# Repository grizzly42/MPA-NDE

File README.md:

# Antenna Deployment Mechanism

## Project Overview
This project is part of the **Nanosatellite Design and Electronics (MPA-NDE 24/25L)** course at **Brno University of Technology (BUT), Faculty of Electrical Engineering and Communication (FEEC)**. Our team is developing an **Antenna Deployment Mechanism** for a CubeSat-class nanosatellite.

## Purpose
The Antenna Deployment Mechanism (ADM) is designed to stow and deploy a flexible metal tape antenna reliably once the satellite reaches its operational orbit. The mechanism ensures the antenna remains secured during launch and deploys upon receiving an activation signal from the microcontroller unit (MCU).

## Key Features
- **Compact and Lightweight Design** – Optimized for CubeSat integration.
- **Reliable Deployment** – Ensures consistent antenna extension in space conditions.
- **Locking Mechanism** – Holds the antenna in place until deployment is required.
- **MCU Controlled Activation** – Deployment triggered via command.

## Components
- **Flexible Metal Tape Antenna**
- **Holding Mechanism (Damping System, Hinges, and Latch)**
- **Microcontroller (MCU) and Activation Circuitry**
- **Sensors for Deployment Verification**

## Block diagram

## SW (Dodělat podle skutečnosti)

```c
   DE2-PROJECT          
   ├── include         // Included file(s)
   │   └── timer.h
   ├── lib             // Libraries
   │   ├── gpio        // Your GPIO library
   │   │   ├── gpio.c
   │   │   └── gpio.h
   │   ├── oled        
   │   │   ├── oled.c
   │   │   ├── oled.h
   │   │   └── font.h
   │   ├── uart       
   │   │   ├── uart.c
   │   │   └── uart.h
   │   ├── twi       
   │   │   ├── twi.c
   │   │   └── twi.h
   │   ├── soil       
   │   │   ├── soil.c
   │   │   └── soil.h
   │   ├── controls       
   │   │   ├── controls.c
   │   │   └── controls.
   │   ├── HumTempSensor       
   │   │   ├── HumTempSensor.c
   │   │   └── HumTempSensor.h
   │   ├── rtc       
   │   │   ├── rtc.c
   │   │   └── rtc.h
   │   ├── display       
   │   │   ├── display.c
   │   │   └── display.h
   │   ├── buttons       
   │   │   ├── buttons.c
   │   │   └── buttons.h
   │   ├── pot       
   │   │   ├── pot.c
   │   │   └── pot.h
   │   └── light       
   │       ├── light.c
   │       └── light.h
   ├── src             // Source file(s)
   │   └── main.c
   ├── test            // No need this
   └── platformio.ini  // Project Configuration File
   ```

## Team
This project is developed by students of **MPA-NDE 24/25L** at BUT FEEC as part of a nanosatellite technology research initiative.

## Future Work
- Prototype development and testing.
- Thermal and mechanical stress analysis.
- Integration with satellite subsystems.

## License
This project is for academic and research purposes under the Nanosatellite Design and Electronics course at BUT.

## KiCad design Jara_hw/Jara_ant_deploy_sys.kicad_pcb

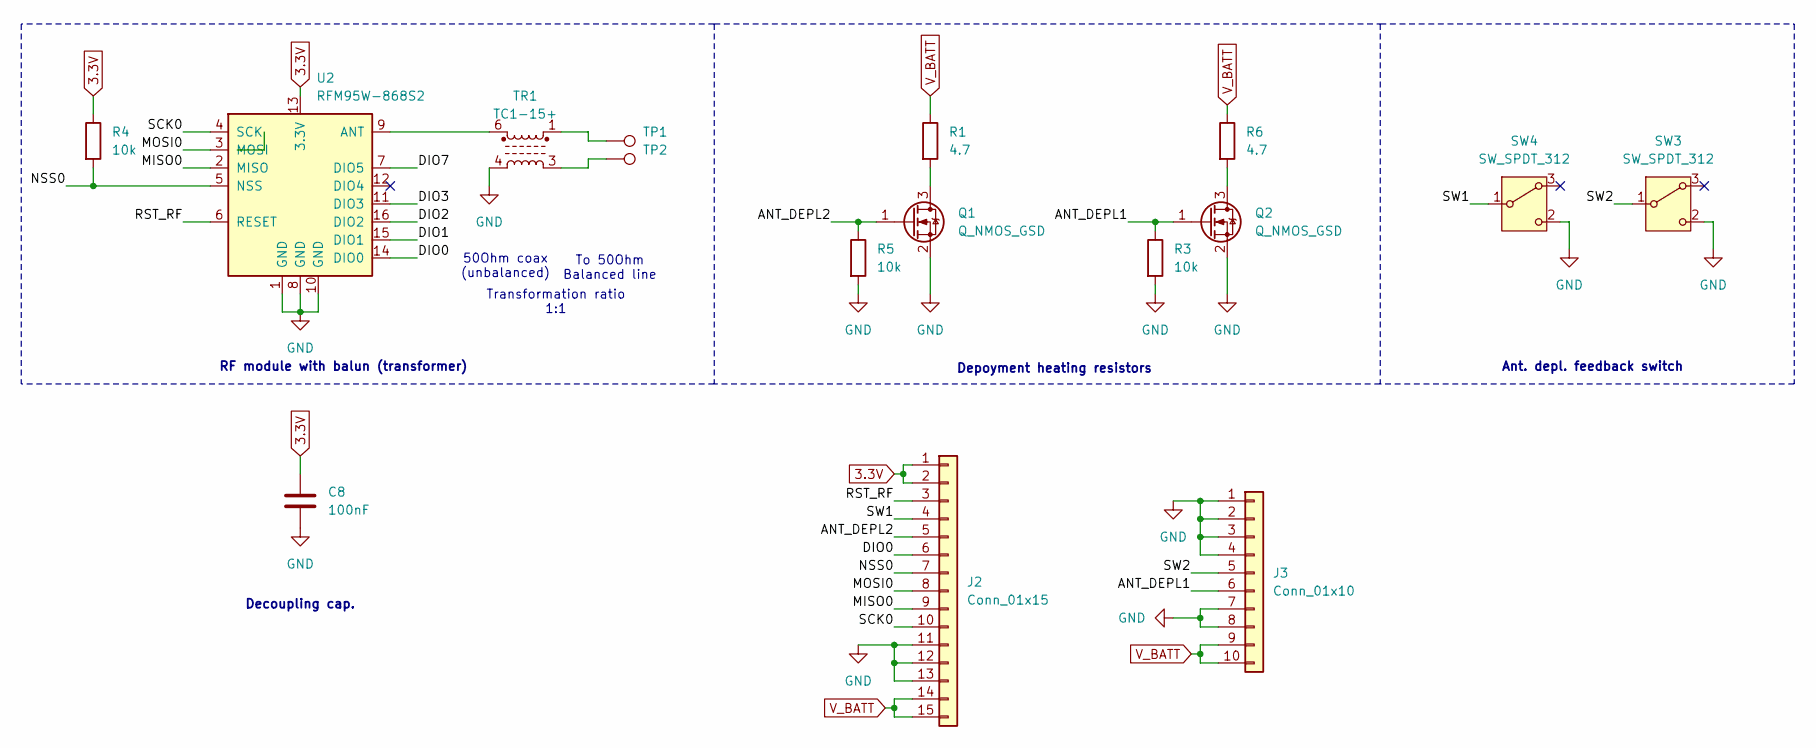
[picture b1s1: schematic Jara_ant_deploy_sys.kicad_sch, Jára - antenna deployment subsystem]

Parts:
C8: 100nF; C_0805_2012Metric
J2: Conn_01x15; PinHeader_1x15_P2.54mm_Vertical
J3: Conn_01x10; PinHeader_1x10_P2.54mm_Vertical
Q1, Q2: Q_NMOS_GSD; SOT-23
R1, R6: 4.7; R_0805_2012Metric
R3, R4, R5: 10k; R_0805_2012Metric
SW3, SW4: SW_SPDT_312; ZMA00A080L04RC
TP1, TP2: TestPoint_Pad_1.5x1.5mm
TR1: TC1-15+; Transformer_MiniCircuits_AT224-1A
U2: RFM95W-868S2; HOPERF_RFM9XW_SMD

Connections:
3.3V: C8.1, J2.1, J2.2, R4.1, U2.13 (3.3V)
/ANT_DEPL1: J3.6, Q2.1 (G), R3.1
/ANT_DEPL2: J2.5, Q1.1 (G), R5.1
/DIO0: J2.6, U2.14 (DIO0)
/DIO1: U2.15 (DIO1)
/DIO2: U2.16 (DIO2)
/DIO3: U2.11 (DIO3)
/DIO7: U2.7 (DIO5)
/MISO0: J2.9, U2.2 (MISO)
/MOSI0: J2.8, U2.3 (MOSI)
/NSS0: J2.7, R4.2, U2.5 (NSS)
/RST_RF: J2.3, U2.6 (RESET)
/SCK0: J2.10, U2.4 (SCK)
/SW1: J2.4, SW4.1 (B)
/SW2: J3.5, SW3.1 (B)
GND: C8.2, J2.11, J2.12, J2.13, J3.1, J3.2, J3.3, J3.4, J3.7, J3.8, Q1.2 (S), Q2.2 (S), R3.2, R5.2, SW3.2 (C), SW4.2 (C), TR1.4, U2.1 (GND), U2.8 (GND), U2.10 (GND)
unnamed: Q1.3 (D), R1.2
unnamed: Q2.3 (D), R6.2
unnamed: TP1.1, TR1.1
unnamed: TP2.1, TR1.3
unnamed: TR1.6, U2.9 (ANT)
V_BATT: J2.14, J2.15, J3.9, J3.10, R1.1, R6.1

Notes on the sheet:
RF module with balun (transformer)
Decoupling cap.
50Ohm coax (unbalanced)
To 50Ohm Balanced line
Ant. depl. feedback switch
Depoyment heating resistors
Transformation ratio 1:1

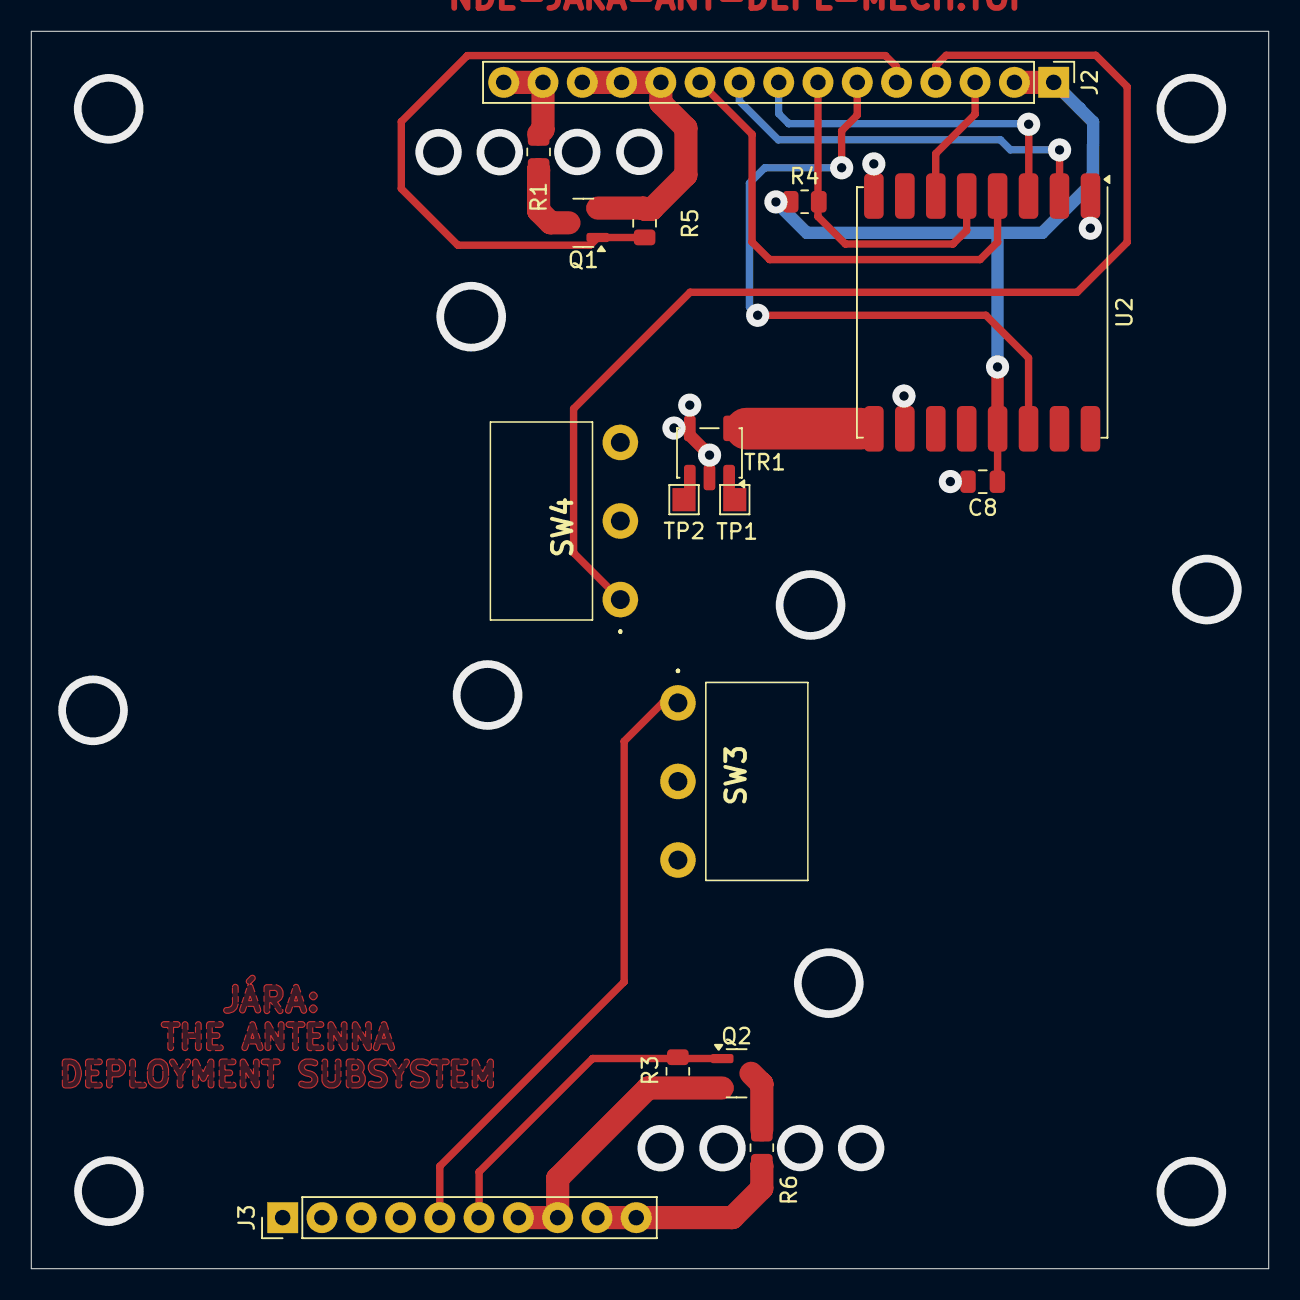
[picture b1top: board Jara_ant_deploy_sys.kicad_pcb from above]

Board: 2 copper layers, 80.0 x 80.0 mm, 16 parts (0 on the bottom side), 18 nets.

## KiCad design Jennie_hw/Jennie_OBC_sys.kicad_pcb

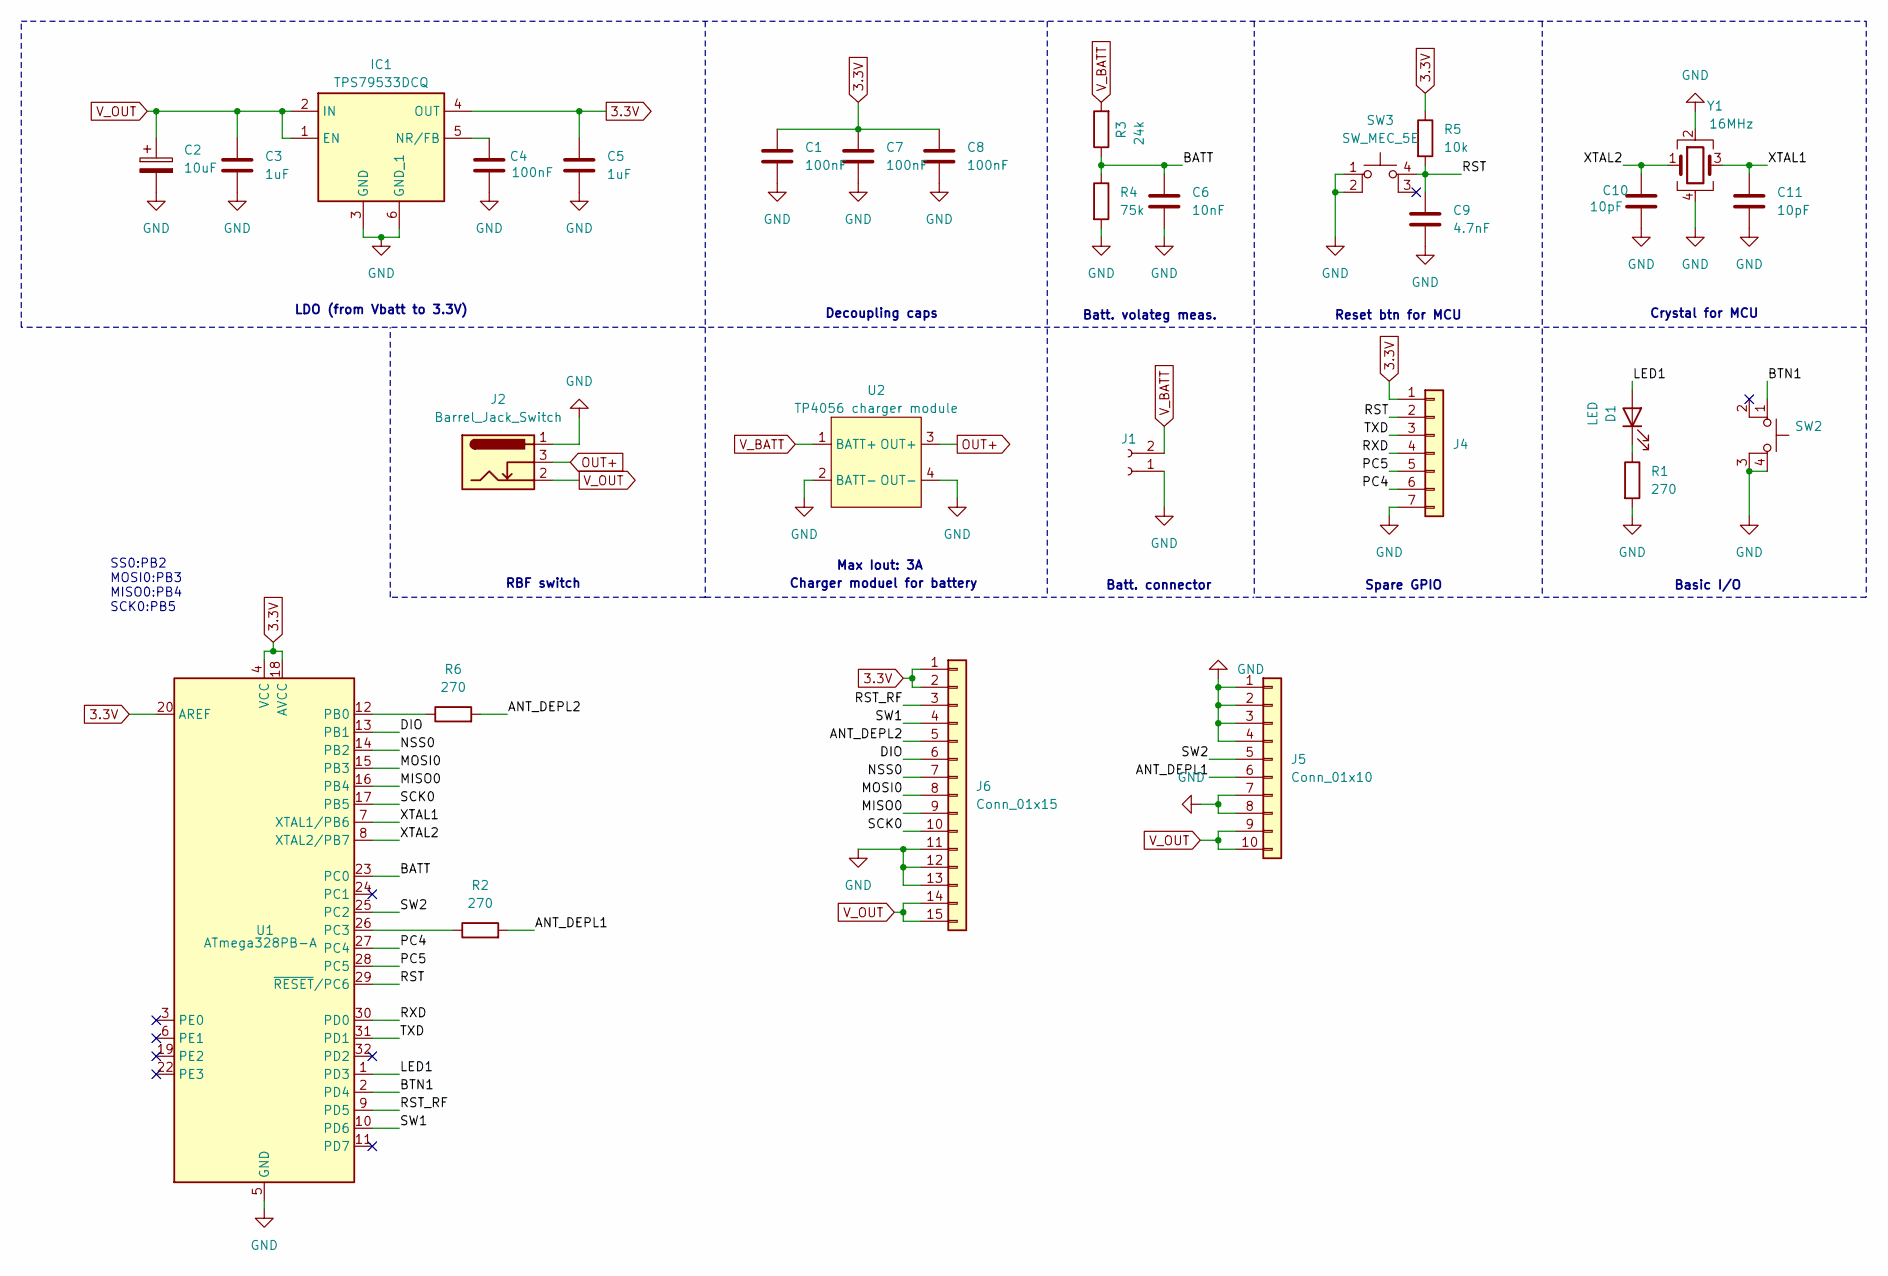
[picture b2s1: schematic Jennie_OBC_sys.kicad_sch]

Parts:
C1, C4, C7, C8: 100nF; C_0805_2012Metric
C2: 10uF; CP_Radial_D5.0mm_P2.50mm
C3, C5: 1uF; C_0805_2012Metric
C6: 10nF; C_0805_2012Metric
C9: 4.7nF; C_0805_2012Metric
C10, C11: 10pF; C_0805_2012Metric
D1: LED; LED_0805_2012Metric
IC1: TPS79533DCQ; SOT-223-6; Mouser Part Number 595-TPS79533DCQ
J1: PinHeader_1x02_P2.54mm_Vertical
J2: Barrel_Jack_Switch; BarrelJack_Horizontal
J4: PinHeader_1x07_P2.54mm_Vertical
J5: Conn_01x10; PinHeader_1x10_P2.54mm_Vertical
J6: Conn_01x15; PinHeader_1x15_P2.54mm_Vertical
R1, R2, R6: 270; R_0805_2012Metric
R3: 24k; R_0805_2012Metric
R4: 75k; R_0805_2012Metric
R5: 10k; R_0805_2012Metric
SW2: 15715272
SW3: SW_MEC_5E; 15715272
U1: ATmega328PB-A; TQFP-32_7x7mm_P0.8mm
U2: TP4056 charger module; TP4056_module
Y1: 16MHz; Crystal_SMD_3225-4Pin_3.2x2.5mm

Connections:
3.3V: C1.1, C5.1, C7.1, C8.1, IC1.4 (OUT), J4.1, J6.1, J6.2, R5.1, U1.4 (VCC), U1.18 (AVCC), U1.20 (AREF)
/ANT_DEPL1: J5.6, R2.2
/ANT_DEPL2: J6.5, R6.2
/BATT: C6.1, R3.1, R4.1, U1.23 (PC0)
/BTN1: SW2.1, U1.2 (PD4)
/DIO: J6.6, U1.13 (PB1)
/LED1: D1.2 (A), U1.1 (PD3)
/MISO0: J6.9, U1.16 (PB4)
/MOSI0: J6.8, U1.15 (PB3)
/NSS0: J6.7, U1.14 (PB2)
/PC4: J4.6, U1.27 (PC4)
/PC5: J4.5, U1.28 (PC5)
/RST: C9.1, J4.2, R5.2, SW3.4 (A), U1.29 (~RESET/PC6)
/RST_RF: J6.3, U1.9 (PD5)
/RXD: J4.4, U1.30 (PD0)
/SCK0: J6.10, U1.17 (PB5)
/SW1: J6.4, U1.10 (PD6)
/SW2: J5.5, U1.25 (PC2)
/TXD: J4.3, U1.31 (PD1)
/XTAL1: C11.1, U1.7 (XTAL1/PB6), Y1.3
/XTAL2: C10.1, U1.8 (XTAL2/PB7), Y1.1
GND: C1.2, C2.2, C3.2, C4.2, C5.2, C6.2, C7.2, C8.2, C9.2, C10.2, C11.2, IC1.3 (GND), IC1.6 (GND_1), J1.1, J2.1, J4.7, J5.1, J5.2, J5.3, J5.4, J5.7, J5.8, J6.11, J6.12, J6.13, R1.2, R4.2, SW2.3 (K), SW2.4 (A), SW3.1, SW3.2, U1.5 (GND), U1.21 (GND), U2.2 (BATT-), U2.4 (OUT-), Y1.2, Y1.4
unnamed: D1.1 (K), R1.1
unnamed: C4.1, IC1.5 (NR/FB)
unnamed: R6.1, U1.12 (PB0)
unnamed: R2.1, U1.26 (PC3)
OUT+: J2.3, U2.3 (OUT+)
V_BATT: J1.2, R3.2, U2.1 (BATT+)
V_OUT: C2.1, C3.1, IC1.1 (EN), IC1.2 (IN), J2.2, J5.9, J5.10, J6.14, J6.15

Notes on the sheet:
Batt. connector
Decoupling caps
Basic I/O
Batt. volateg meas.
Charger moduel for battery
Spare GPIO
Max Iout: 3A
RBF switch
Crystal for MCU
Reset btn for MCU
SS0:PB2 MOSI0:PB3 MISO0:PB4 SCK0:PB5
LDO (from Vbatt to 3.3V)

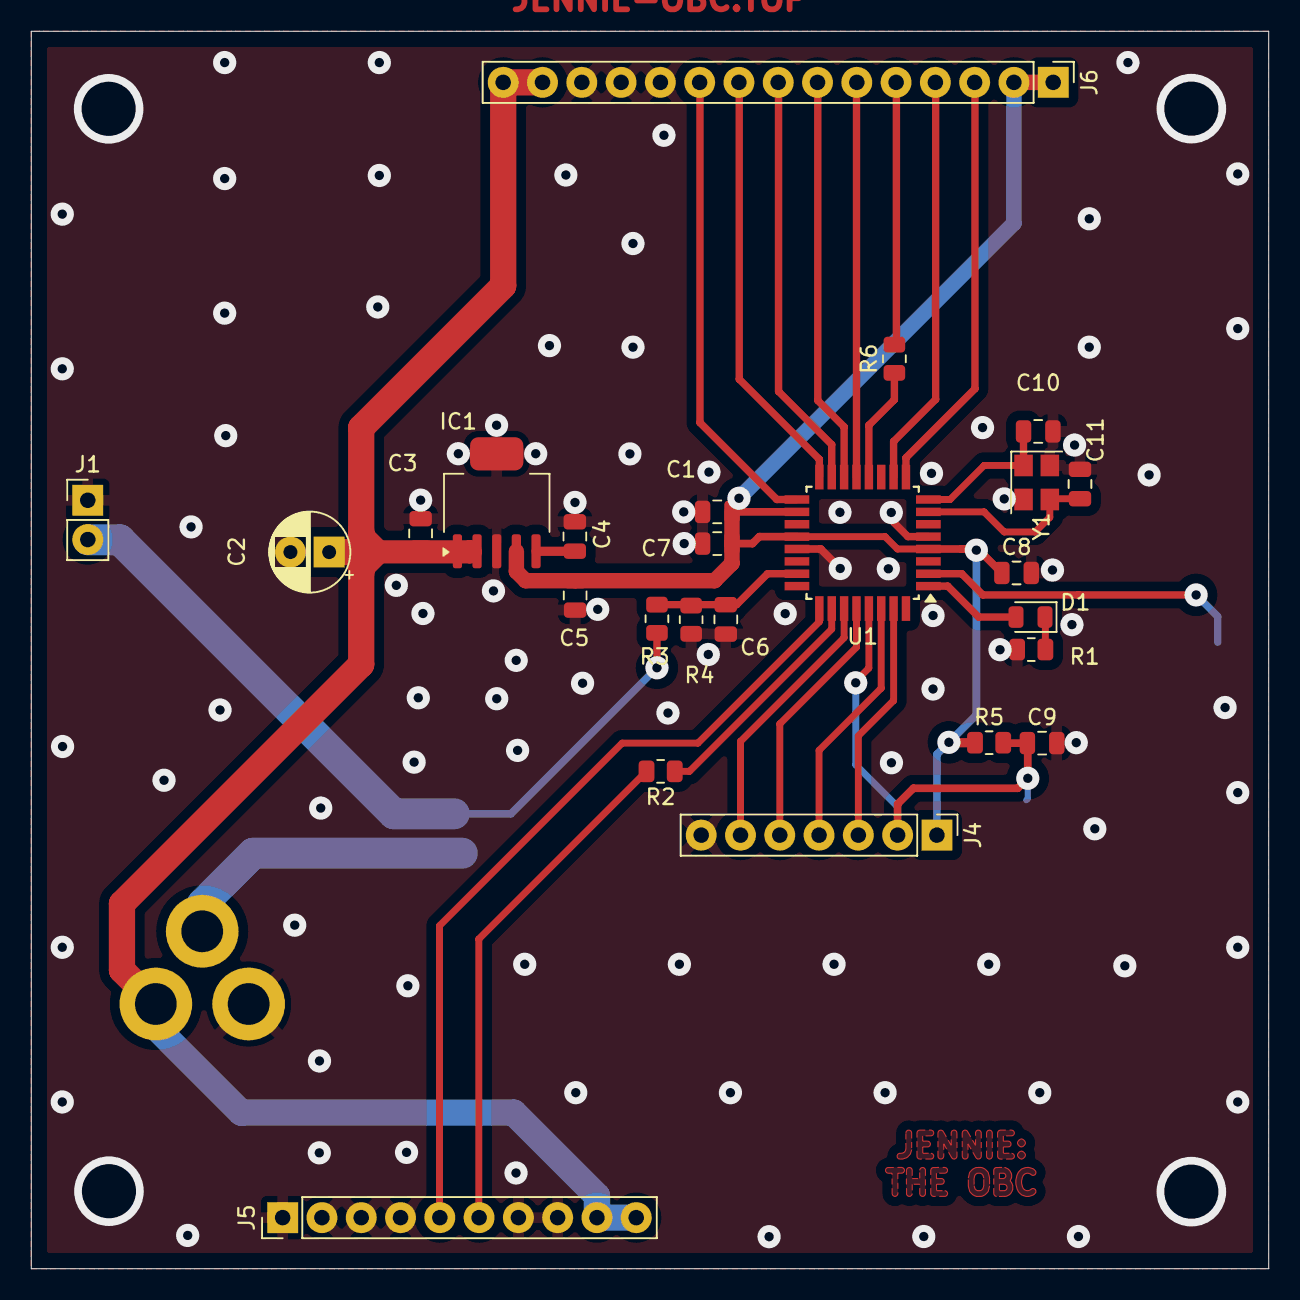
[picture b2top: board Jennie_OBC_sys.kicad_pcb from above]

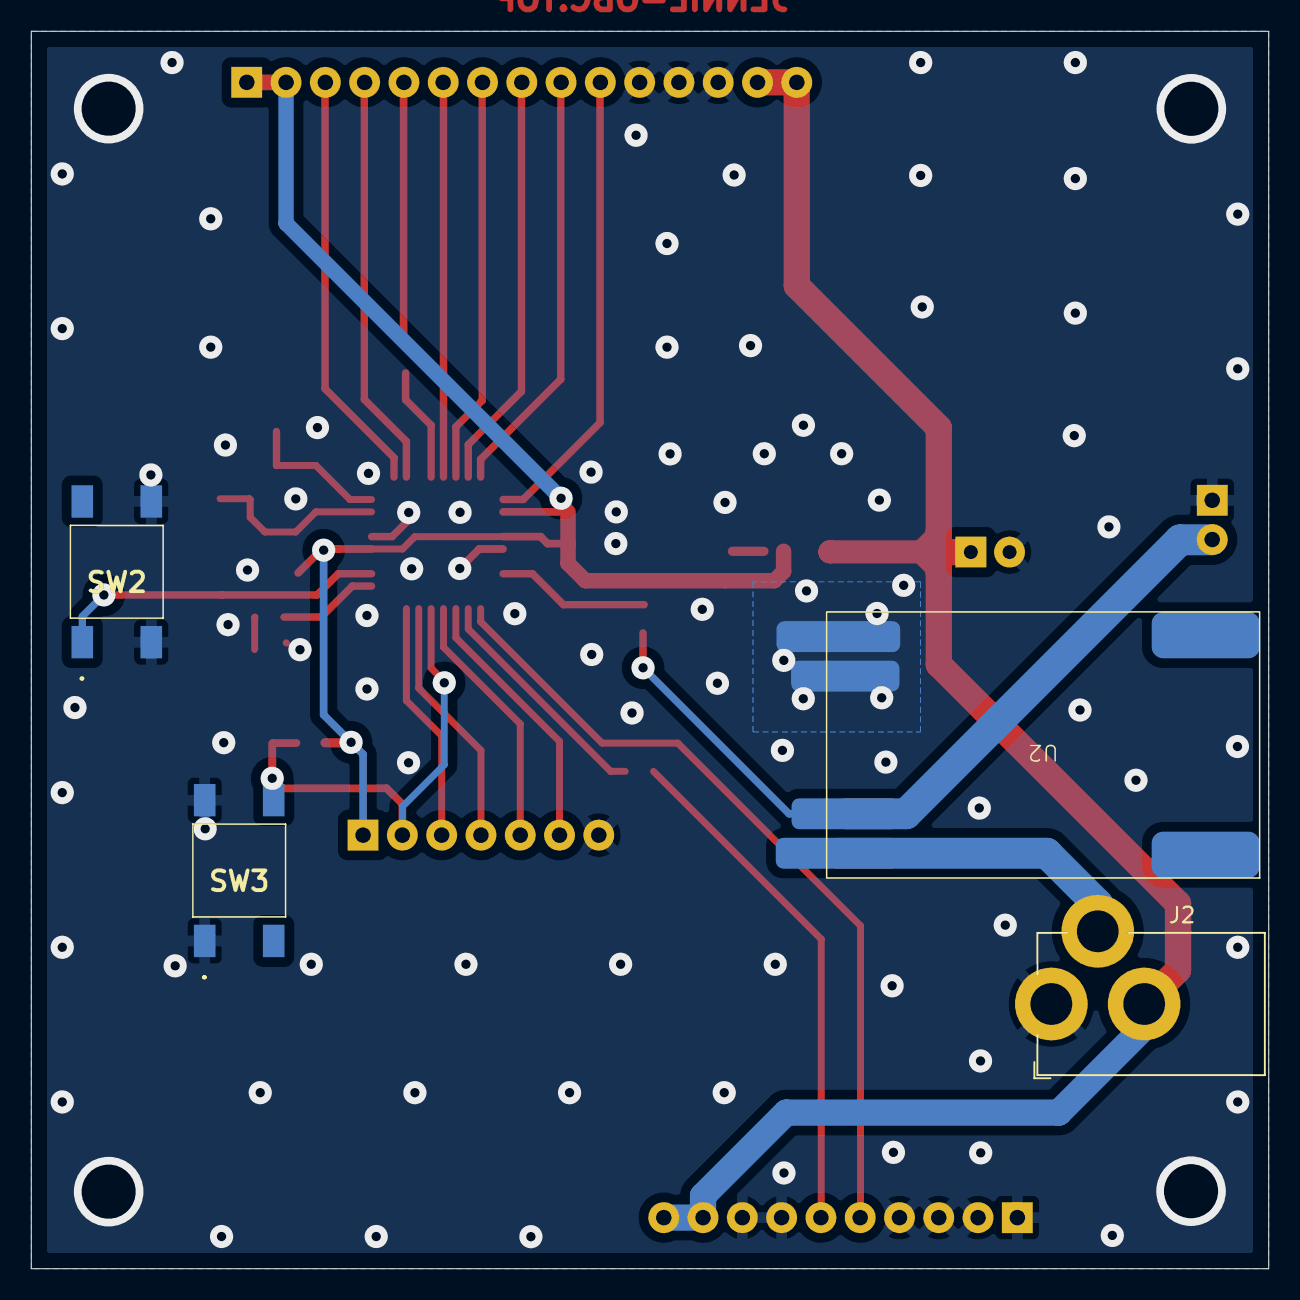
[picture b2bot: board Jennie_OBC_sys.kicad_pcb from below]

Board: 2 copper layers, 80.0 x 80.0 mm, 29 parts (4 on the bottom side), 29 nets.

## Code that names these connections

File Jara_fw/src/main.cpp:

// #include <avr/io.h>
// #include <util/delay.h>
// #include <stdbool.h>

// // Definice pinů
// #define END_SWITCH1_PIN PD6
// #define END_SWITCH2_PIN PC2
// #define BURN_PIN1      PC3
// #define BURN_PIN2      PB0
// #define BUTTON_PIN     PD4
// #define LED_PIN        PD3  // LED signalizace

// bool antennaDeployed = false;

// // UART inicializace (9600 baud, 8N1)
// void uart_init(void) {
//     uint16_t ubrr = 103;
//     UBRR0H = (uint8_t)(ubrr >> 8);
//     UBRR0L = (uint8_t)ubrr;
//     UCSR0B = (1 << TXEN0);
//     UCSR0C = (1 << UCSZ01) | (1 << UCSZ00);
// }

// void uart_putchar(char c) {
//     while (!(UCSR0A & (1 << UDRE0)));
//     UDR0 = c;
// }

// void uart_print(const char *s) {
//     while (*s) {
//         uart_putchar(*s++);
//     }
// }

// void setup() {
//     // Vstupy
//     DDRD &= ~(1 << END_SWITCH1_PIN);
//     DDRC &= ~(1 << END_SWITCH2_PIN);
//     DDRD &= ~(1 << BUTTON_PIN);

//     // Pull-up rezistory
//     PORTD |= (1 << END_SWITCH1_PIN);
//     PORTC |= (1 << END_SWITCH2_PIN);
//     PORTD |= (1 << BUTTON_PIN);

//     // Výstupy
//     DDRC |= (1 << BURN_PIN1);
//     DDRB |= (1 << BURN_PIN2);
//     DDRD |= (1 << LED_PIN);

//     PORTC &= ~(1 << BURN_PIN1);
//     PORTB &= ~(1 << BURN_PIN2);
//     PORTD &= ~(1 << LED_PIN);

//     uart_init();
//     uart_print("System initialized\r\n");
// }

// bool isEndSwitchPressed() {
//     return !(PIND & (1 << END_SWITCH1_PIN)) && !(PINC & (1 << END_SWITCH2_PIN));
// }

// bool isButtonPressed() {
//     return !(PIND & (1 << BUTTON_PIN));
// }

// void burnWire() {
//     uart_print("Burning wire...\r\n");
//     PORTC |= (1 << BURN_PIN1);
//     PORTB |= (1 << BURN_PIN2);
//     _delay_ms(1000);
//     PORTC &= ~(1 << BURN_PIN1);
//     PORTB &= ~(1 << BURN_PIN2);
//     uart_print("Burn complete\r\n");
// }

// int main(void) {
//     setup();

//     while (1) {
//         if (isEndSwitchPressed() && !antennaDeployed) {
//             uart_print("Antenna ready for deployment\r\n");

//             /*
//             uart_print("Waiting for button press...\r\n");
//             while (!isButtonPressed()) {
//                 // čekáme na stisk tlačítka
//             }
//             uart_print("Button pressed, starting countdown...\r\n");
//             */

//             uart_print("Countdown started\r\n");
//             for (int i = 0; i < 100; i++) {
//                 _delay_ms(100);
//             }

//             burnWire();
//             antennaDeployed = true;

//             uart_print("posílám data\r\n");
//             PORTD |= (1 << LED_PIN); // Zapni LED signalizaci
//         }

//         if (antennaDeployed) {
//             // případná další logika
//         }
//     }
// }



// #include <avr/io.h>
// #include <util/delay.h>

// #define LED_PIN PD3  // PD3 odpovídá fyzickému pinu 5

// int main(void) {
//     DDRD |= (1 << LED_PIN); // Nastaví PD3 jako výstup

//     while (1) {
//         PORTD ^= (1 << LED_PIN); // Přepne stav LED
//         _delay_ms(500);          // Počká 500 ms
//     }

//     return 0;
// }


/*
* Author: David Kolet-Tassara
* Date:   July 26, 2016
* Rev:    1.1
* Description:
*   This sketch uses the RadioHead library to send and receive messages via the
*   RFM95W LoRa Packet Radio sold by Adafruit. More information on the radio may
*   be found here: https://www.adafruit.com/product/3072
*   Uses the Serial Monitor of the Arduino IDE as the message console.
* Part List:
*   Arduino/Genuino Uno
*   RFM95W LoRa Packet Radio
*   Edge-Launch SMA Connector for 1.6mm / 0.062" Thick PCBs
*   Right-angle Mini GSM/Cellular Quad-Band Antenna - 2dBi SMA Plug
* Attribution:
*   Parts of the code were taken from the tutorial for the RFM9x LoRa Packet Radio
*   written by Limor Fried (ladyada).
*   RadioHead Libraries were written by Mike McCauley.
*   http://www.airspayce.com/mikem/arduino/RadioHead/index.html
*   
*   //TODO
*   1.  Review code comments
*/

#include <SPI.h>
#include <RH_RF95.h>

#define RFM95_CS 10
#define RFM95_RST 9
#define RFM95_INT 2
#define RF95_FREQ 915.0 //acceptable values are 868 or 915 MHz
#define RF95_PWR 23 //acceptable range includes all integers between 5 and 23 dBm
String OPERATOR = "DKT"; //name of the user sending from this console

RH_RF95 rf95(RFM95_CS, RFM95_INT);

String message="";

void setup() {
  pinMode(RFM95_RST, OUTPUT);
  digitalWrite(RFM95_RST, HIGH);
 
  while (!Serial);
  Serial.begin(9600);
  delay(100);
 
  Serial.println("Booting LoRa Radio");
 
  // manual reset
  digitalWrite(RFM95_RST, LOW);
  delay(10);
  digitalWrite(RFM95_RST, HIGH);
  delay(10);
 
  while (!rf95.init()) {
    Serial.println("LoRa Radio Init Failed");
    while (1);
  }
  Serial.println("LoRa Radio OK!");

  // Defaults after init are 434.0MHz, 13dBm, Bw = 125 kHz, Cr = 4/5, Sf = 128chips/symbol, CRC on
  // The default transmitter power is 13dBm, using PA_BOOST.
  // If you are using RFM95/96/97/98 modules which uses the PA_BOOST transmitter pin, then 
  // you can set transmitter powers from 5 to 23 dBm:
 
  // Defaults after init are 434.0MHz, modulation GFSK_Rb250Fd250, +13dbM
  if (!rf95.setFrequency(RF95_FREQ)) {
    Serial.println("setFrequency failed");
    while (1);
  }
  Serial.print("Freq set to: "); Serial.print(RF95_FREQ); Serial.println("MHz");
  
  rf95.setTxPower(RF95_PWR, false);
  Serial.print("TXPower set to: "); Serial.print(RF95_PWR); Serial.println("dBm");

  Serial.println("Ready!");
}

void loop() {
  
  message=Serial.readString();

  if (message != "") {

    message = OPERATOR+": "+message;
     
    //explode string to char array for sending
    int messageSize = message.length()+1;
    char radiopacket[messageSize];
    message.toCharArray(radiopacket, messageSize);

    //send the message OTA
    Serial.println("Sending..."); delay(10);
    rf95.send((uint8_t *)radiopacket, messageSize);
    delay(10);
    rf95.waitPacketSent();

    //report and clean up
    Serial.println(message);
    message="";
    
  } else {

    uint8_t buf[RH_RF95_MAX_MESSAGE_LEN];
    uint8_t len = sizeof(buf);

    if (rf95.recv(buf, &len))
    {
      //RH_RF95::printBuffer("Received: ", buf, len);
      Serial.println((char*)buf);
      Serial.print("RSSI: "); Serial.println(rf95.lastRssi(), DEC);
    }
  }
}

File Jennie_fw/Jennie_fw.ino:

#include <SPI.h>
#include <LoRa.h>

#include "pakety.h"

#define LED PD3        // LED pro výstup
#define BTN PD4        // Tlačítko pro aktivaci

#define SWITCH1_PIN 16  // Koncový spínač 1
#define OUTPUT1_PIN 17  // Výstup pro spínač 1

#define SWITCH2_PIN 6  // Koncový spínač 2
#define OUTPUT2_PIN 8  // Výstup pro spínač 2

#define PROG_EN PC4
#define JUST_GND PC5

#define TIMEOUT 5000  // Timeout v ms

#define BW 125E3
#define TXPWR 10 // in dBm
#define SF 12 //spreading factor

bool start_depl = false;
unsigned long timeout_state = 0;
bool output1_active = false;
bool output2_active = false;

const float referenceVoltage = 3.3;   // nebo 5.0, podle toho, co přivádíš na AREF
const float voltageDividerRatio = 72.0 / (24.0 + 72.0);

int counter = 0;
int p_counter = 0;

void setup() {
  Serial.begin(9600);

  pinMode(SWITCH1_PIN, INPUT_PULLUP);
  pinMode(SWITCH2_PIN, INPUT_PULLUP);

  pinMode(OUTPUT1_PIN, OUTPUT);
  pinMode(OUTPUT2_PIN, OUTPUT);

  pinMode(LED, OUTPUT);
  pinMode(BTN, INPUT_PULLUP);

  pinMode(PROG_EN, INPUT_PULLUP);
  pinMode(JUST_GND, OUTPUT);
  digitalWrite(JUST_GND, LOW);

  digitalWrite(LED, LOW);
  digitalWrite(OUTPUT1_PIN, LOW);
  digitalWrite(OUTPUT2_PIN, LOW);

  if (!LoRa.begin(868E6)) {
    Serial.println("Starting LoRa failed!");
    while (1);
  } else {
    Serial.println("Starting LoRa succeed");
  }

  // Bezpečnostní pojistka, pokud nechceme deployment
  while (digitalRead(PROG_EN) == LOW) {
    Serial.println("Programming wire connected");
    delay(1000);
  }


  LoRa.setSignalBandwidth(BW);
  LoRa.setTxPower(TXPWR);
  LoRa.setSpreadingFactor(SF);

  // Signalizace zapnutí
  digitalWrite(LED, HIGH);
  delay(1000);
  digitalWrite(LED, LOW);
  Serial.println("setup ok");

}

void loop() {
  delay(30);
  Serial.println("loop start");
  if (digitalRead(BTN) == LOW || !start_depl) {
    start_depl = true;
    Serial.println("Tlačítko stisknuto, start!");

    // Aktivace výstupů
    digitalWrite(LED, HIGH);
    //digitalWrite(OUTPUT1_PIN, HIGH);
    //digitalWrite(OUTPUT2_PIN, HIGH);

    output1_active = true;
    output2_active = true;
  }

  if (start_depl) {
    Serial.println("Depl start");
    // Kontrola výstupu 1
    if (output1_active) {
      if (digitalRead(SWITCH1_PIN) == HIGH) {
        digitalWrite(OUTPUT1_PIN, LOW);
        output1_active = false;
        Serial.println("OUTPUT 1 OFF");
      }
    }

    // Kontrola výstupu 2
    if (output2_active) {
      if (digitalRead(SWITCH2_PIN) == HIGH) {
        digitalWrite(OUTPUT2_PIN, LOW);
        output2_active = false;
        Serial.println("OUTPUT 2 OFF");
      }
    }
    if (!output1_active && !output2_active) {
      //start_depl = false;

      delay(5000);

      int raw = analogRead(PC0); // nebo A0
      float voltageADC = (raw / 1023.0) * referenceVoltage;
      float batteryVoltage = voltageADC / voltageDividerRatio;

      digitalWrite(LED, LOW);
      Serial.println("Sekvence dokončena.");

      Serial.print("Sending packet: ");
      Serial.println(counter);

      // send packet
      LoRa.beginPacket();

      LoRa.print("pct n. ");
      LoRa.println(counter);

      LoRa.print("VBatt: ");
      LoRa.println(batteryVoltage);

      LoRa.println(pakety[p_counter]);

      LoRa.endPacket();

      if (p_counter >= packet_count - 1) {
        p_counter = 0;
      } else {
        p_counter++;
      }
      counter++;
    }
  }
}

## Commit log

2025-03-06 nefunguje
2025-03-06 Jara and Jennie subsystems HW added, not finished yet
2025-03-06 Jennie and Jára PCBs prepared for manufacturing(?)
2025-03-06 3D models of Jára and Jennie PCBs added
2025-03-09 Push buttons moved to bottom side, STEP model of TP4056 added
2025-03-11 remove before start switch added
2025-03-11 cleaning up the schematics
2025-03-13 IBOM added
2025-03-24 funguje platformIO (mě)
    Pokud to někdo rozchodíte u sebe, jste hustý, mě to aktuálně zapíná config z arduina IDE, ale ten command pouští platformIO přes terminal XD
2025-03-25 Nástřel FW
    Nástřel FW, asi nějak ready na testování
2025-03-26 fw pro arduinko
2025-04-03 small fix of small routing error on Jennie PCB (V_batt routed to different pins on pinheader to maintain compatibility with Jára pinheader)
2025-04-07 Měříme napětí celkem
    Ahooooj :)
2025-04-07 Posíláme napětí baterky
2025-04-07 naajs
2025-04-10 Úpravy kódu 1
2025-04-10 few changes in FW
2025-04-17 ahoooooj
2025-04-17 lora jede někde ve fw je issue
2025-04-22 jennie_fw_V2 done
2025-05-11 Minor changes in PCB design
2025-05-11 DIO7 changed to DIO0 on Jára PCB to be compatibile with the LoRa Arduino library
2025-05-11 antenna model
2025-05-11 3D models push
